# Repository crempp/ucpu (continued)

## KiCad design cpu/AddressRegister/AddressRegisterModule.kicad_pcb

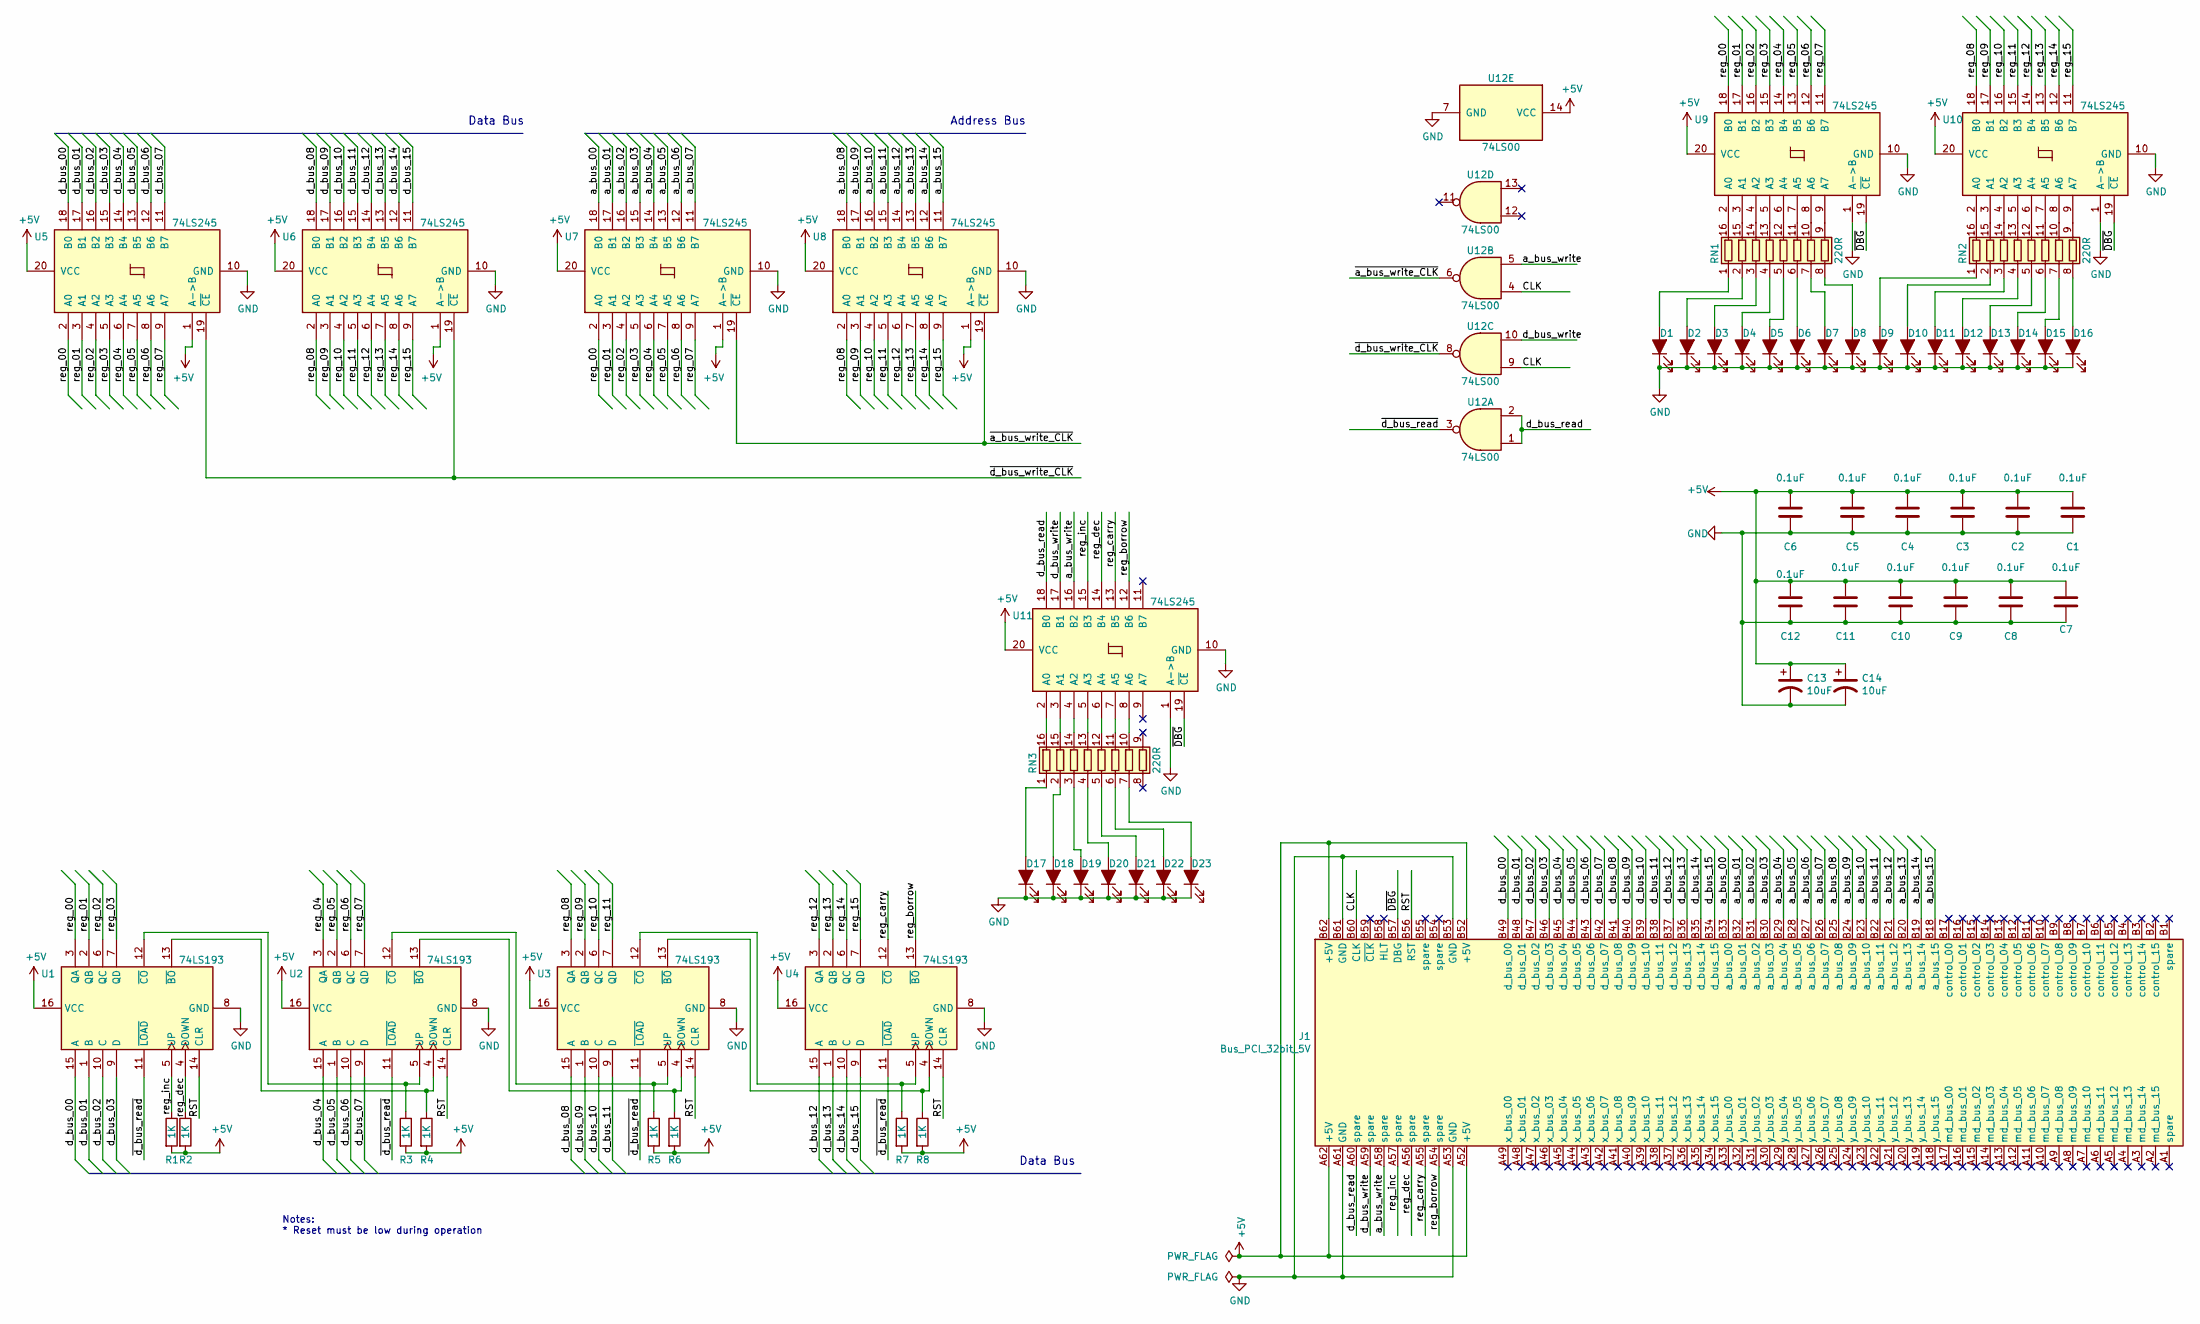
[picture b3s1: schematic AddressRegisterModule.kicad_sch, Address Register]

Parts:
C1, C2, C3, C4, C5, C6, C7, C8, C9, C10, C11, C12: 0.1uF; C_0603_1608Metric_Pad1.05x0.95mm_HandSolder; Digikey 399-1096-1-ND
C13, C14: 10uF; CP_Elec_4x5.4; Digikey 493-9786-1-ND
D1, D2, D3, D4, D5, D6, D7, D8, D9, D10, D11, D12, D13, D14, D15, D16: D_RED; LED_1206_3216Metric_Pad1.42x1.75mm_HandSolder; Digikey 732-4991-1-ND
D17, D18, D19, D20, D21, D22, D23: D_AMBER; LED_1206_3216Metric_Pad1.42x1.75mm_HandSolder; Digikey 732-4994-1-ND
J1: Bus_PCI_32bit_5V; BUS_PCI
R1, R2, R3, R4, R5, R6, R7, R8: 1K; R_0603_1608Metric_Pad0.98x0.95mm_HandSolder
RN1, RN2, RN3: 220R; R_Array_Convex_8x0602; Digikey Y1221CT-ND
U1, U2, U3, U4: 74LS193; SOIC-16_3.9x9.9mm_P1.27mm; Digikey 1727-7973-1-ND
U5, U6, U7, U8, U9, U10, U11: 74LS245; SOIC-20W_7.5x12.8mm_P1.27mm; Digikey 296-1208-1-ND
U12: 74LS00; SOIC-14_3.9x8.7mm_P1.27mm; Digikey 296-14860-1-ND

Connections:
+5V: C1.2, C2.2, C3.2, C4.2, C5.2, C6.2, C7.2, C8.2, C9.2, C10.2, C11.2, C12.2, C13.1, C14.1, J1.A52 (+5V), J1.A62 (+5V), J1.B52 (+5V), J1.B62 (+5V), R1.2, R2.2, R3.2, R4.2, R5.2, R6.2, R7.2, R8.2, U1.16 (VCC), U2.16 (VCC), U3.16 (VCC), U4.16 (VCC), U5.1 (A->B), U5.20 (VCC), U6.1 (A->B), U6.20 (VCC), U7.1 (A->B), U7.20 (VCC), U8.1 (A->B), U8.20 (VCC), U9.20 (VCC), U10.20 (VCC), U11.20 (VCC), U12.14 (VCC)
/CLK: J1.B60 (CLK), U12.4, U12.9
/RST: J1.B56 (RST), U1.14 (CLR), U2.14 (CLR), U3.14 (CLR), U4.14 (CLR)
/a_bus_00: J1.B33 (a_bus_00), U7.18 (B0)
/a_bus_01: J1.B32 (a_bus_01), U7.17 (B1)
/a_bus_02: J1.B31 (a_bus_02), U7.16 (B2)
/a_bus_03: J1.B30 (a_bus_03), U7.15 (B3)
/a_bus_04: J1.B29 (a_bus_04), U7.14 (B4)
/a_bus_05: J1.B28 (a_bus_05), U7.13 (B5)
/a_bus_06: J1.B27 (a_bus_06), U7.12 (B6)
/a_bus_07: J1.B26 (a_bus_07), U7.11 (B7)
/a_bus_08: J1.B25 (a_bus_08), U8.18 (B0)
/a_bus_09: J1.B24 (a_bus_09), U8.17 (B1)
/a_bus_10: J1.B23 (a_bus_10), U8.16 (B2)
/a_bus_11: J1.B22 (a_bus_11), U8.15 (B3)
/a_bus_12: J1.B21 (a_bus_12), U8.14 (B4)
/a_bus_13: J1.B20 (a_bus_13), U8.13 (B5)
/a_bus_14: J1.B19 (a_bus_14), U8.12 (B6)
/a_bus_15: J1.B18 (a_bus_15), U8.11 (B7)
/a_bus_write: J1.A58 (spare), U11.16 (B2), U12.5
/d_bus_00: J1.B49 (d_bus_00), U1.15 (A), U5.18 (B0)
/d_bus_01: J1.B48 (d_bus_01), U1.1 (B), U5.17 (B1)
/d_bus_02: J1.B47 (d_bus_02), U1.10 (C), U5.16 (B2)
/d_bus_03: J1.B46 (d_bus_03), U1.9 (D), U5.15 (B3)
/d_bus_04: J1.B45 (d_bus_04), U2.15 (A), U5.14 (B4)
/d_bus_05: J1.B44 (d_bus_05), U2.1 (B), U5.13 (B5)
/d_bus_06: J1.B43 (d_bus_06), U2.10 (C), U5.12 (B6)
/d_bus_07: J1.B42 (d_bus_07), U2.9 (D), U5.11 (B7)
/d_bus_08: J1.B41 (d_bus_08), U3.15 (A), U6.18 (B0)
/d_bus_09: J1.B40 (d_bus_09), U3.1 (B), U6.17 (B1)
/d_bus_10: J1.B39 (d_bus_10), U3.10 (C), U6.16 (B2)
/d_bus_11: J1.B38 (d_bus_11), U3.9 (D), U6.15 (B3)
/d_bus_12: J1.B37 (d_bus_12), U4.15 (A), U6.14 (B4)
/d_bus_13: J1.B36 (d_bus_13), U4.1 (B), U6.13 (B5)
/d_bus_14: J1.B35 (d_bus_14), U4.10 (C), U6.12 (B6)
/d_bus_15: J1.B34 (d_bus_15), U4.9 (D), U6.11 (B7)
/d_bus_read: J1.A60 (spare), U11.18 (B0), U12.1, U12.2
/d_bus_write: J1.A59 (spare), U11.17 (B1), U12.10
/reg_00: U1.3 (QA), U5.2 (A0), U7.2 (A0), U9.18 (B0)
/reg_01: U1.2 (QB), U5.3 (A1), U7.3 (A1), U9.17 (B1)
/reg_02: U1.6 (QC), U5.4 (A2), U7.4 (A2), U9.16 (B2)
/reg_03: U1.7 (QD), U5.5 (A3), U7.5 (A3), U9.15 (B3)
/reg_04: U2.3 (QA), U5.6 (A4), U7.6 (A4), U9.14 (B4)
/reg_05: U2.2 (QB), U5.7 (A5), U7.7 (A5), U9.13 (B5)
/reg_06: U2.6 (QC), U5.8 (A6), U7.8 (A6), U9.12 (B6)
/reg_07: U2.7 (QD), U5.9 (A7), U7.9 (A7), U9.11 (B7)
/reg_08: U3.3 (QA), U6.2 (A0), U8.2 (A0), U10.18 (B0)
/reg_09: U3.2 (QB), U6.3 (A1), U8.3 (A1), U10.17 (B1)
/reg_10: U3.6 (QC), U6.4 (A2), U8.4 (A2), U10.16 (B2)
/reg_11: U3.7 (QD), U6.5 (A3), U8.5 (A3), U10.15 (B3)
/reg_12: U4.3 (QA), U6.6 (A4), U8.6 (A4), U10.14 (B4)
/reg_13: U4.2 (QB), U6.7 (A5), U8.7 (A5), U10.13 (B5)
/reg_14: U4.6 (QC), U6.8 (A6), U8.8 (A6), U10.12 (B6)
/reg_15: U4.7 (QD), U6.9 (A7), U8.9 (A7), U10.11 (B7)
/reg_borrow: J1.A54 (spare), U4.13 (~BO), U11.12 (B6)
/reg_carry: J1.A55 (spare), U4.12 (~CO), U11.13 (B5)
/reg_dec: J1.A56 (spare), R2.1, U1.4 (DOWN), U11.14 (B4)
/reg_inc: J1.A57 (spare), R1.1, U1.5 (UP), U11.15 (B3)
/~DBG: J1.B57 (DBG), U9.19 (~CE), U10.19 (~CE), U11.19 (~CE)
/~a_bus_write_CLK: U7.19 (~CE), U8.19 (~CE), U12.6
/~d_bus_read: U1.11 (~LOAD), U2.11 (~LOAD), U3.11 (~LOAD), U4.11 (~LOAD), U12.3
/~d_bus_write_CLK: U5.19 (~CE), U6.19 (~CE), U12.8
GND: C1.1, C2.1, C3.1, C4.1, C5.1, C6.1, C7.1, C8.1, C9.1, C10.1, C11.1, C12.1, C13.2, C14.2, D1.1 (K), D2.1 (K), D3.1 (K), D4.1 (K), D5.1 (K), D6.1 (K), D7.1 (K), D8.1 (K), D9.1 (K), D10.1 (K), D11.1 (K), D12.1 (K), D13.1 (K), D14.1 (K), D15.1 (K), D16.1 (K), D17.1 (K), D18.1 (K), D19.1 (K), D20.1 (K), D21.1 (K), D22.1 (K), D23.1 (K), J1.A53 (GND), J1.A61 (GND), J1.B53 (GND), J1.B61 (GND), U1.8 (GND), U2.8 (GND), U3.8 (GND), U4.8 (GND), U5.10 (GND), U6.10 (GND), U7.10 (GND), U8.10 (GND), U9.1 (A->B), U9.10 (GND), U10.1 (A->B), U10.10 (GND), U11.1 (A->B), U11.10 (GND), U12.7 (GND)
unnamed: D1.2 (A), RN1.1 (R1.1)
unnamed: D2.2 (A), RN1.2 (R2.1)
unnamed: D3.2 (A), RN1.3 (R3.1)
unnamed: D4.2 (A), RN1.4 (R4.1)
unnamed: D5.2 (A), RN1.5 (R5.1)
unnamed: D6.2 (A), RN1.6 (R6.1)
unnamed: D7.2 (A), RN1.7 (R7.1)
unnamed: D8.2 (A), RN1.8 (R8.1)
unnamed: D9.2 (A), RN2.1 (R1.1)
unnamed: D10.2 (A), RN2.2 (R2.1)
unnamed: D11.2 (A), RN2.3 (R3.1)
unnamed: D12.2 (A), RN2.4 (R4.1)
unnamed: D13.2 (A), RN2.5 (R5.1)
unnamed: D14.2 (A), RN2.6 (R6.1)
unnamed: D15.2 (A), RN2.7 (R7.1)
unnamed: D16.2 (A), RN2.8 (R8.1)
unnamed: D17.2 (A), RN3.1 (R1.1)
unnamed: D18.2 (A), RN3.2 (R2.1)
unnamed: D19.2 (A), RN3.3 (R3.1)
unnamed: D20.2 (A), RN3.4 (R4.1)
unnamed: D21.2 (A), RN3.5 (R5.1)
unnamed: D22.2 (A), RN3.6 (R6.1)
unnamed: D23.2 (A), RN3.7 (R7.1)
unnamed: R3.1, U1.12 (~CO), U2.5 (UP)
unnamed: R4.1, U1.13 (~BO), U2.4 (DOWN)
unnamed: R5.1, U2.12 (~CO), U3.5 (UP)
unnamed: R6.1, U2.13 (~BO), U3.4 (DOWN)
unnamed: R7.1, U3.12 (~CO), U4.5 (UP)
unnamed: R8.1, U3.13 (~BO), U4.4 (DOWN)
unnamed: RN1.9 (R8.2), U9.9 (A7)
unnamed: RN1.10 (R7.2), U9.8 (A6)
unnamed: RN1.11 (R6.2), U9.7 (A5)
unnamed: RN1.12 (R5.2), U9.6 (A4)
unnamed: RN1.13 (R4.2), U9.5 (A3)
unnamed: RN1.14 (R3.2), U9.4 (A2)
unnamed: RN1.15 (R2.2), U9.3 (A1)
unnamed: RN1.16 (R1.2), U9.2 (A0)
unnamed: RN2.9 (R8.2), U10.9 (A7)
unnamed: RN2.10 (R7.2), U10.8 (A6)
unnamed: RN2.11 (R6.2), U10.7 (A5)
unnamed: RN2.12 (R5.2), U10.6 (A4)
unnamed: RN2.13 (R4.2), U10.5 (A3)
unnamed: RN2.14 (R3.2), U10.4 (A2)
unnamed: RN2.15 (R2.2), U10.3 (A1)
unnamed: RN2.16 (R1.2), U10.2 (A0)
unnamed: RN3.10 (R7.2), U11.8 (A6)
unnamed: RN3.11 (R6.2), U11.7 (A5)
unnamed: RN3.12 (R5.2), U11.6 (A4)
unnamed: RN3.13 (R4.2), U11.5 (A3)
unnamed: RN3.14 (R3.2), U11.4 (A2)
unnamed: RN3.15 (R2.2), U11.3 (A1)
unnamed: RN3.16 (R1.2), U11.2 (A0)

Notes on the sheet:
Data Bus
Notes: * Reset must be low during operation
Address Bus

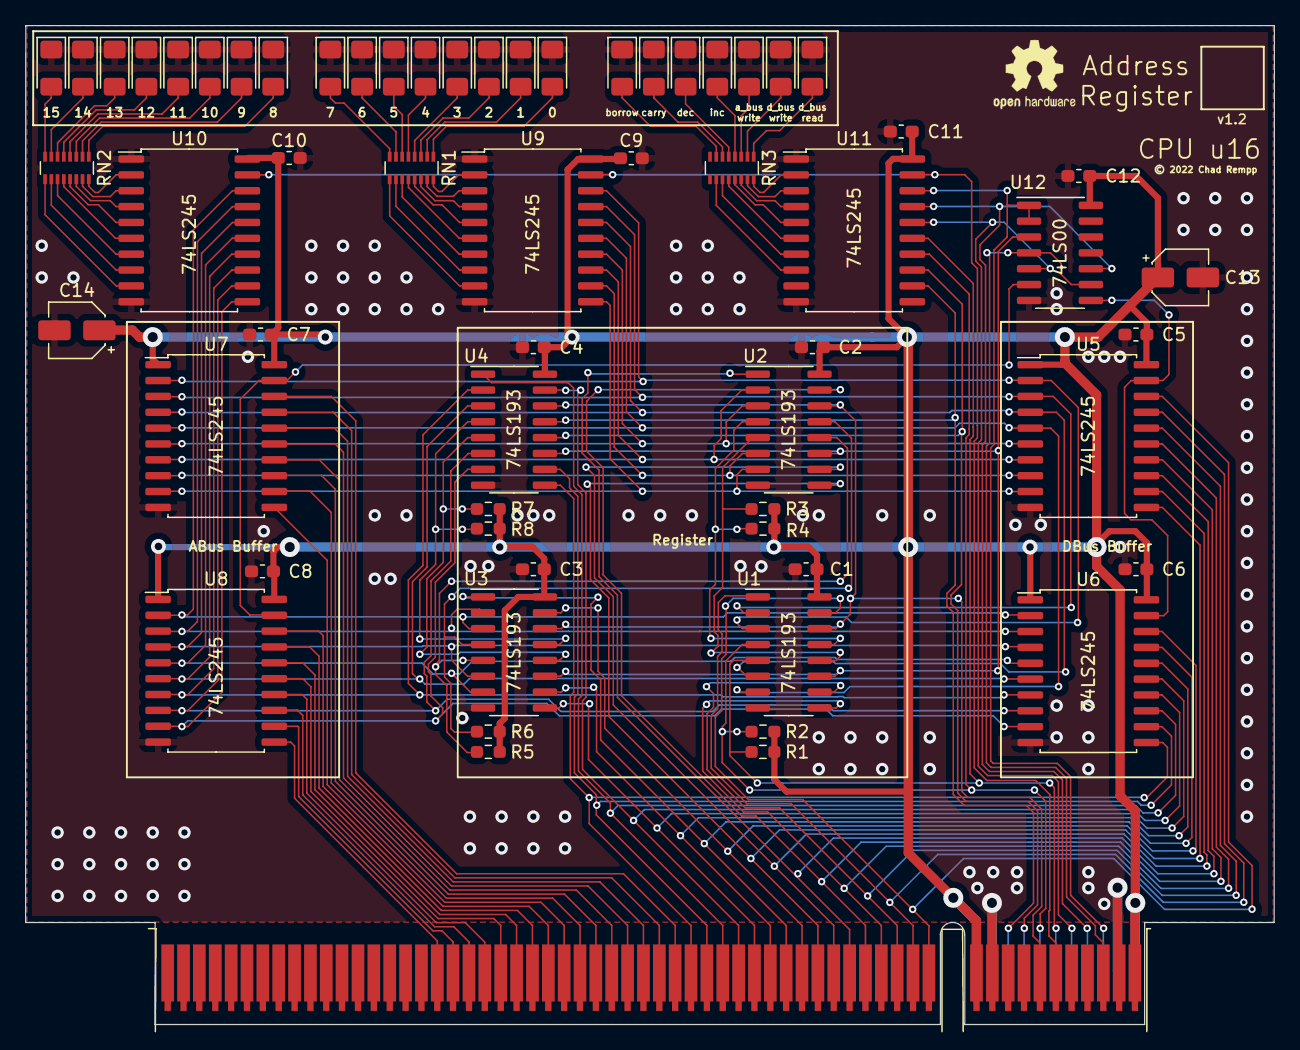
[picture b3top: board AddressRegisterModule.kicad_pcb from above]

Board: 2 copper layers, 100.0 x 80.0 mm, 61 parts (0 on the bottom side), 115 nets.
